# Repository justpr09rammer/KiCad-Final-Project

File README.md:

# IoT-Based AC Ceiling Fan Regulator  

## 📝 Description  
This project is an **IoT-based AC Ceiling Fan Regulator** that allows you to control the speed of your ceiling fan using an **Android application**. The circuit regulates fan speed by adjusting the **phase angle of the AC sine wave** using a **TRIAC**, controlled via **PWM signals** from an **ESP8266 (NodeMCU)**. The system integrates **Firebase Realtime Database** for cloud-based control, enabling remote adjustments via a mobile app.  

### 🔧 Key Features  
- **Wi-Fi Controlled** – Adjust fan speed remotely via an Android app.  
- **Phase Angle Control** – Uses TRIAC for efficient AC power regulation.  
- **Zero-Crossing Detection** – Ensures smooth switching and reduces noise.  
- **Firebase Integration** – Real-time updates for seamless control.  
- **Safe Isolation** – Optocouplers provide electrical isolation between high-voltage AC and low-voltage control circuits.  

## 🛠 Hardware Components  
| Component | Quantity |  
|-----------|----------|  
| ESP8266 (NodeMCU) | 1 |  
| NE555 Timer IC | 1 |  
| TRIAC (BT136) | 1 |  
| MOC3021 Opto-TRIAC Driver | 1 |  
| PC817 Optocoupler | 1 |  
| IRF9540 P-Channel MOSFET | 1 |  
| 1N4007 Diodes | 4 |  
| 56K, 1W Resistors | 2 |  
| 10K Resistors | 5 |  
| 82K Resistor | 1 |  
| 470Ω Resistors | 2 |  
| 47Ω Resistors | 2 |  
| 1000µF, 25V Capacitor | 1 |  
| 3.3µF Capacitor | 1 |  
| 0.1µF, 1KV Capacitor | 1 |  
| AMS1117-3.3V Regulator | 1 |  
| DC Power Jack | 1 |  
| Screw Terminal (5.04mm) | 2 |  

## 📡 Circuit Diagram & PCB Design  
The circuit consists of:  
1. **ESP8266 (Wi-Fi Control)** – Generates PWM for speed control.  
2. **Zero-Crossing Detector** – Provides sync for TRIAC triggering.  
3. **555 Timer (Monostable Mode)** – Controls TRIAC firing angle.  
4. **TRIAC & Snubber Circuit** – Regulates AC power to the fan.  
5. **Low-Pass Filter** – Converts PWM to analog for MOSFET control.  

🔗 **PCB Design**: Made in **Eagle CAD** (Gerber files available).  

## 📲 Software & Firebase Setup  
1. **Arduino IDE** – Used to program the ESP8266.  
2. **Firebase Realtime Database** – Stores fan speed values.  
3. **Android App** – Sends speed adjustments to Firebase.  

### 🔄 How Data Flow Works:  
- **Android App** → **Firebase DB** → **ESP8266** → **PWM Signal** → **555 Timer** → **TRIAC** → **Fan Speed Control**  

## ⚙️ Installation & Setup  
### 🔌 Hardware Setup  
1. Assemble the PCB as per the schematic.  
2. Connect **220V AC input** (ensure proper insulation).  
3. Power the circuit using a **3.3V DC supply**.  
4. Connect the fan to the output terminals.  

### 💻 Software Setup  
1. **Flash ESP8266** with the provided Arduino code.  
2. Configure **Firebase Realtime Database** and update credentials in the code.  
3. Install the **Android app** and link it to Firebase.  

## 📱 Android App Control  
- **Slider-based interface** for adjusting fan speed (0% to 100%).  
- Real-time updates via Firebase.  

## ⚠️ Safety Notes  
- **High Voltage Warning!** – This circuit works with **220V AC**. Handle with care.  
- Use proper **insulation** and **enclosure** for safety.  
- Ensure **correct grounding** to avoid electric shocks.  

## 📂 Repository Contents  
- `Circuit_Schematic/` – Eagle PCB design & Gerber files.  
- `Arduino_Code/` – ESP8266 Firebase & PWM control code.  
- `Android_App/` – APK or source code for the control app.  
- `Docs/` – Datasheets & additional references.  

## 🚀 Future Improvements  
- **Voice Control** (Alexa/Google Assistant integration).  
- **Multi-fan control** (Expandable to multiple channels).  
- **Energy Monitoring** (Track power consumption).  

## 📜 License  
**MIT License** – Open-source for educational & personal use.  

---

🌟 **Give it a ⭐ if you find this project useful!**  

---  
**Happy Building!** 🔧⚡  

---  

---

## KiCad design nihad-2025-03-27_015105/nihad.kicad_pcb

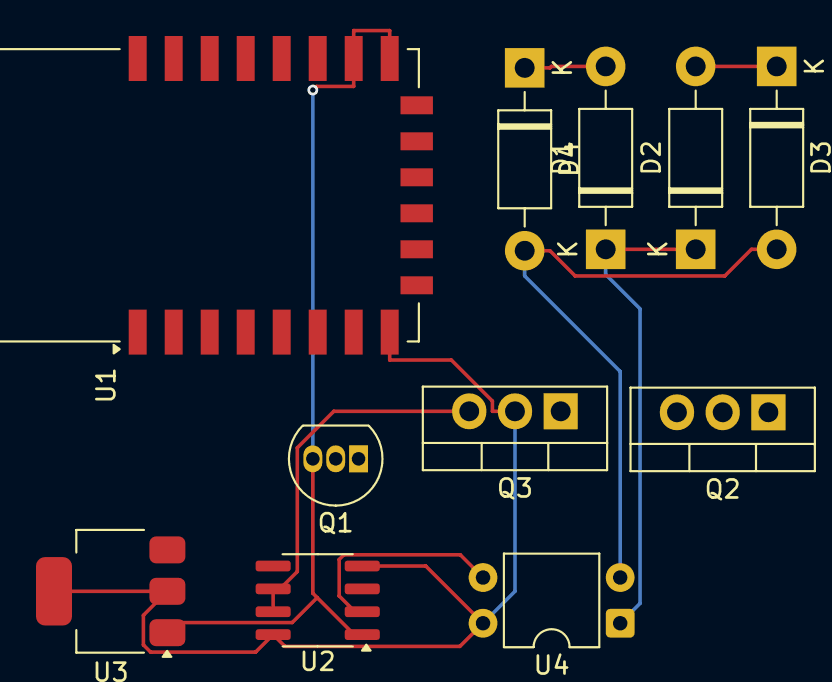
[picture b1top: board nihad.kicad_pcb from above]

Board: 2 copper layers, 11 parts (0 on the bottom side), 8 nets.

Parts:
D1, D2: D_DO-41_SOD81_P10.16mm_Horizontal
D3, D4: 1N4007; D_DO-41_SOD81_P10.16mm_Horizontal
Q1: BC548; TO-92_Inline
Q2: BT136-500; TO-220-3_Vertical
Q3: IRF9540N; TO-220-3_Vertical
U1: ESP-12E
U2: NE555D; SOIC-8_3.9x4.9mm_P1.27mm
U3: AMS1117-3.3; SOT-223-3_TabPin2
U4: PC817; DIP-4_W7.62mm

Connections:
+3.3V: Q3.2 (D), U1.8 (VCC), U2.4 (R), U2.8 (VCC), U3.2 (VO), U4.4
CTRL_IN: Q3.3 (S), U2.6 (THR), U2.7 (DIS)
GND: Q1.3 (E), U1.15 (GND), U1.16 (GPIO15), U2.1 (GND), U3.1 (GND)
unnamed: D1.2 (A), D4.1 (K)
unnamed: D1.1 (K), D2.1 (K), U4.1
unnamed: D2.2 (A), D3.1 (K)
unnamed: D3.2 (A), D4.2 (A), U4.2
unnamed: U2.2 (TR), U4.3
